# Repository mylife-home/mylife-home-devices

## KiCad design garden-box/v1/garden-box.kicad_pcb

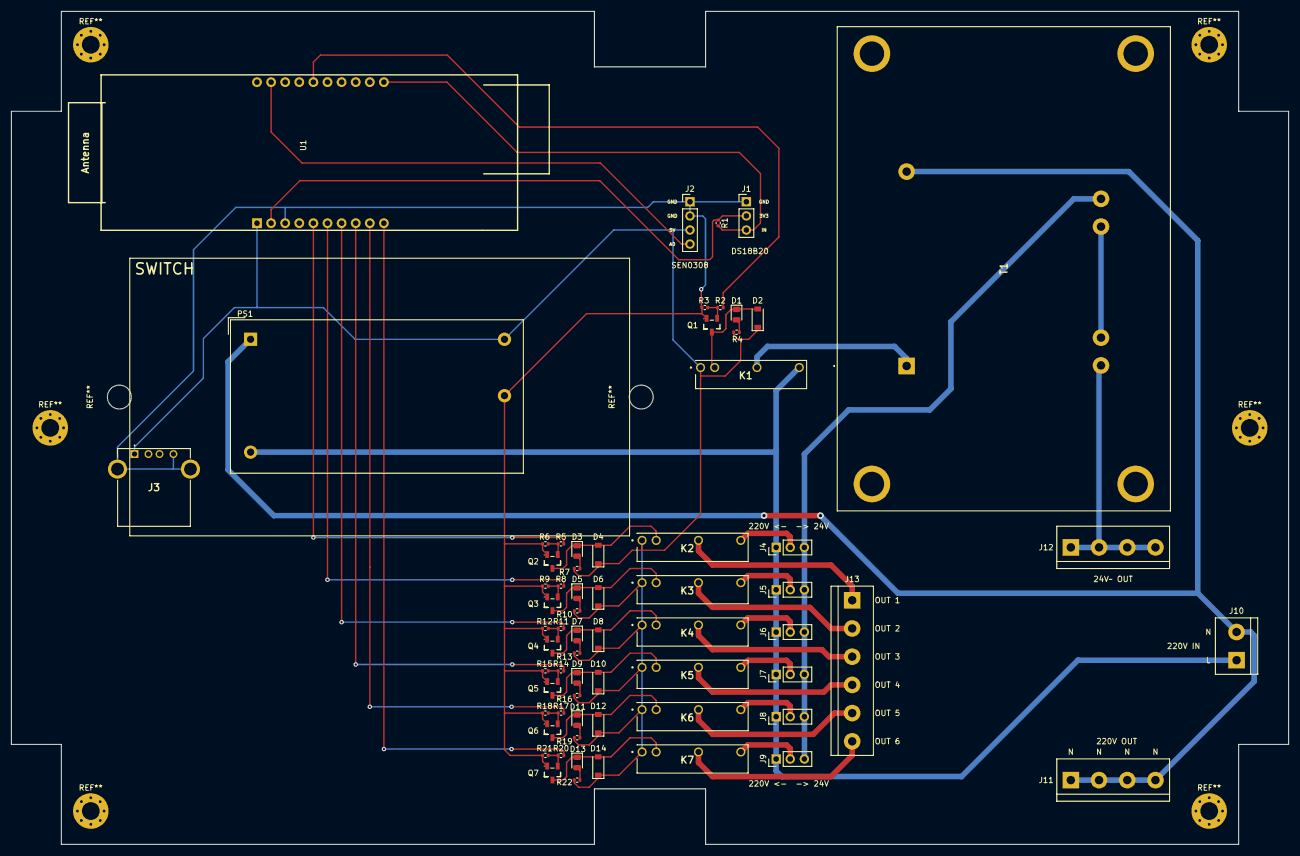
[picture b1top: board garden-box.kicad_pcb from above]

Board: 2 copper layers, 230.0 x 150.0 mm, 66 parts (0 on the bottom side), 51 nets.

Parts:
D1, D3, D5, D7, D9, D11, D13: LED; D_0805_2012Metric
D2, D4, D6, D8, D10, D12, D14: 1N4148; D_SOD-123
J1, J4, J5, J6, J7, J8, J9: Conn_01x03_Male; PinHeader_1x03_P2.54mm_Vertical
J2: Conn_01x04_Male; PinHeader_1x04_P2.54mm_Vertical
J3: USB_A; 875200010BLF
J10: Screw_Terminal_01x02; TerminalBlock_bornier-2_P5.08mm
J11, J12: Screw_Terminal_01x04; TerminalBlock_bornier-4_P5.08mm
J13: Screw_Terminal_01x06; TerminalBlock_bornier-6_P5.08mm
K1, K2, K3, K4, K5, K6, K7: G6DN-1A-L_DC5; G6DN-1A-L
PS1: RS PRO 5V 2A
Q1, Q2, Q3, Q4, Q5, Q6, Q7: 2N3904; SOT-23-3_L2.9-W1.3-P1.90-LS2.4-TR
R1: 4.7KΩ; R_0402_1005Metric
R2, R4, R5, R7, R8, R10, R11, R13, R14, R16, R17, R19, R20, R22: 1KΩ; R_0402_1005Metric
R3, R6, R9, R12, R15, R18, R21: 10KΩ; R_0402_1005Metric
T1: Transformer_1P_2S; VCM36212
U1: ESP32-POE

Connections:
+3V3: J1.2, R1.1, U1.2 (+3.3V_(out))
+5V: D2.1 (K), D4.1 (K), D6.1 (K), D8.1 (K), D10.1 (K), D12.1 (K), D14.1 (K), J2.3, J3.1 (VBUS), K1.1, K2.1, K3.1, K4.1, K5.1, K6.1, K7.1, PS1.4 (+Vo), R4.1, R7.1, R10.1, R13.1, R16.1, R19.1, R22.1, U1.1 (+5V)
/R1: R5.2, U1.5 (GPIO0)
/R2: R8.2, U1.6 (GPIO1)
/R3: R11.2, U1.7 (GPIO2)
/R4: R14.2, U1.8 (GPIO3)
/R5: R17.2, U1.9 (GPIO4)
/R6: R20.2, U1.10 (GPIO5)
/relay 1/Output 1: J4.2, K2.8
/relay 1/Output 2: J13.1, K2.5
/relay 2/Output 1: J5.2, K3.8
/relay 2/Output 2: J13.2, K3.5
/relay 3/Output 1: J6.2, K4.8
/relay 3/Output 2: J13.3, K4.5
/relay 4/Output 1: J7.2, K5.8
/relay 4/Output 2: J13.4, K5.5
/relay 5/Output 1: J8.2, K6.8
/relay 5/Output 2: J13.5, K6.5
/relay 6/Output 1: J9.2, K7.8
/relay 6/Output 2: J13.6, K7.5
/relay transfo/Logic input: R2.2, U1.16 (GPIO33)
/relay transfo/Output 1: J4.1, J5.1, J6.1, J7.1, J8.1, J9.1, J10.1, K1.8, PS1.2 (AC/L)
/relay transfo/Output 2: K1.5, T1.1 (AA)
GND: J1.1, J2.1, J2.2, J3.4 (GND), J3.5 (Shield), PS1.3 (-Vo), Q1.1 (E), Q2.1 (E), Q3.1 (E), Q4.1 (E), Q5.1 (E), Q6.1 (E), Q7.1 (E), R3.2, R6.2, R9.2, R12.2, R15.2, R18.2, R21.2, U1.3 (GND)
unnamed: D1.1 (K), D2.2 (A), K1.2, Q1.3 (C)
unnamed: D1.2 (A), R4.2
unnamed: D3.1 (K), D4.2 (A), K2.2, Q2.3 (C)
unnamed: D3.2 (A), R7.2
unnamed: D5.1 (K), D6.2 (A), K3.2, Q3.3 (C)
unnamed: D5.2 (A), R10.2
unnamed: D7.1 (K), D8.2 (A), K4.2, Q4.3 (C)
unnamed: D7.2 (A), R13.2
unnamed: D9.2 (A), R16.2
unnamed: D9.1 (K), D10.2 (A), K5.2, Q5.3 (C)
unnamed: D11.1 (K), D12.2 (A), K6.2, Q6.3 (C)
unnamed: D11.2 (A), R19.2
unnamed: D13.1 (K), D14.2 (A), K7.2, Q7.3 (C)
unnamed: D13.2 (A), R22.2
unnamed: J1.3, R1.2, U1.11 (GPIO13)
unnamed: J2.4, U1.19 (GPIO36)
unnamed: J4.3, J5.3, J6.3, J7.3, J8.3, J9.3, T1.3 (SA)
unnamed: J10.2, J11.1, J11.2, J11.3, J11.4, PS1.1 (AC/N), T1.2 (AB)
unnamed: J12.1, J12.2, J12.3, J12.4, T1.6 (SD)
unnamed: Q1.2 (B), R2.1, R3.1
unnamed: Q2.2 (B), R5.1, R6.1
unnamed: Q3.2 (B), R8.1, R9.1
unnamed: Q4.2 (B), R11.1, R12.1
unnamed: Q5.2 (B), R14.1, R15.1
unnamed: Q6.2 (B), R17.1, R18.1
unnamed: Q7.2 (B), R20.1, R21.1
unnamed: T1.4 (SB), T1.5 (SC)

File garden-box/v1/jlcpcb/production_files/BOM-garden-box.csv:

Comment,Designator,Footprint,LCSC
1KΩ,"R10,R11,R13,R14,R16,R17,R19,R2,R20,R22,R4,R5,R7,R8",R_0402_1005Metric,C11702
2N3904,"Q1,Q2,Q3,Q4,Q5,Q6,Q7",SOT-23-3_L2.9-W1.3-P1.90-LS2.4-TR,C18536
LED,"D1,D11,D13,D3,D5,D7,D9",D_0805_2012Metric,C2297
10KΩ,"R12,R15,R18,R21,R3,R6,R9",R_0402_1005Metric,C25744
4.7KΩ,R1,R_0402_1005Metric,C25900
1N4148,"D10,D12,D14,D2,D4,D6,D8",D_SOD-123,C81598
Conn_01x03_Male,J4,PinHeader_1x03_P2.54mm_Vertical,
RS PRO 5V 2A,PS1,RS PRO 5V 2A,
Screw_Terminal_01x04,J11,TerminalBlock_bornier-4_P5.08mm,
Conn_01x03_Male,J8,PinHeader_1x03_P2.54mm_Vertical,
G6DN-1A-L_DC5,K6,G6DN-1A-L,
Conn_01x03_Male,J9,PinHeader_1x03_P2.54mm_Vertical,
ESP32-POE,U1,ESP32-POE,
Conn_01x04_Male,J2,PinHeader_1x04_P2.54mm_Vertical,
USB_A,J3,875200010BLF,
G6DN-1A-L_DC5,K2,G6DN-1A-L,
Conn_01x03_Male,J1,PinHeader_1x03_P2.54mm_Vertical,
Screw_Terminal_01x04,J12,TerminalBlock_bornier-4_P5.08mm,
Transformer_1P_2S,T1,VCM36212,
Screw_Terminal_01x06,J13,TerminalBlock_bornier-6_P5.08mm,
Conn_01x03_Male,J5,PinHeader_1x03_P2.54mm_Vertical,
G6DN-1A-L_DC5,K7,G6DN-1A-L,
Conn_01x03_Male,J7,PinHeader_1x03_P2.54mm_Vertical,
G6DN-1A-L_DC5,K3,G6DN-1A-L,
G6DN-1A-L_DC5,K5,G6DN-1A-L,
Conn_01x03_Male,J6,PinHeader_1x03_P2.54mm_Vertical,
G6DN-1A-L_DC5,K4,G6DN-1A-L,
G6DN-1A-L_DC5,K1,G6DN-1A-L,
Screw_Terminal_01x02,J10,TerminalBlock_bornier-2_P5.08mm,
